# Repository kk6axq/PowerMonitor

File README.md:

# Power Monitor
This is a power management board for small robotics applications. This project was
developed as part of an honors contract for EGR216, electrical fundamentals,
during my Spring 2021 semester at Arizona State University, under the guidance
of Dr. Ayan Mallik.

# Purpose
The purpose of this project was to interface with a LiPo battery for a robotics
project I am developing in another course. The purpose of the board was to
prevent issues stemming from over discharge of the battery or accidental shorting.
As LiPo batteries are capable of delivering a large amount of current,
I wanted to prevent circuit damage in the case of short circuit conditions while
also preventing battery damage if I forgot to turn off the robot.
Additionally, I wanted to explore an alternative to the LM7805 I had used in
previous projects to provide a high current 5V supply for a planned payload bay
on the robot.
# Features
* Variety of current protection features:
  * Overcurrent up to 10A
  * Overvoltage detection up to 25V
  * Undervoltage detection
  * Short circuit protection
* Independent load control. Load, and 5V load supply can be switched on or off by the onboard microcontroller.
* Provides 5V at up to 3A and 12V at up to 10A burst.
* Dual power supplies for load and onboard microcontroller.
* Serial based monitoring and control of load switch, power status, and fault conditions.
* Onboard RGB LED for status indication
* Open source software.
* Hardware schematic and layout is open source. Project files are currently not available due to licensing restrictions.
# Design Criteria
* 12V power source or 3s LiPo battery
* Provide 12V at 4.2A from battery and 5V at 1.5A
* Monitor for fault conditions, including overvoltage, undervoltage, overcurrent, and short circuit
* Report faults to the robot's main microcontroller

# Core components:
* ATTiny88 microcontroller programmed with Arduino and the ATTinyCore
* ACS722 Current Sensor with +/- 10A current measuring capacity
* Voltage divider based voltage sensor with 25V measuring capability
* Dual LM2576 5V buck converter
* MIC5504 3.3V regulator for current sensor
* Si4435 P-Channel MOSFET for short circuit protection and load switching

# Repository Structure:
The repository is organized by folder, as shown below.
## Hardware
The hardware folder contains the KiCAD project files and output Gerbers and PDFs
for easy viewing. It includes:
* PDF schematic
* STEP file of PCB
* Bill of Materials
* Interactive HTML BOM for PCB assembly
* KiCAD project files
* Archive of Gerber board files and PDF of PCB layers

## Software
The software folder contains the code used to enable the power management behaviors.
## Docs
The docs folder contains documentation of the digital communications protocol and an explanation of the operation of the device.

# License
This project is copyright (C) 2021 by Lukas Severinghaus. It is licensed under the GNU GPLV3.

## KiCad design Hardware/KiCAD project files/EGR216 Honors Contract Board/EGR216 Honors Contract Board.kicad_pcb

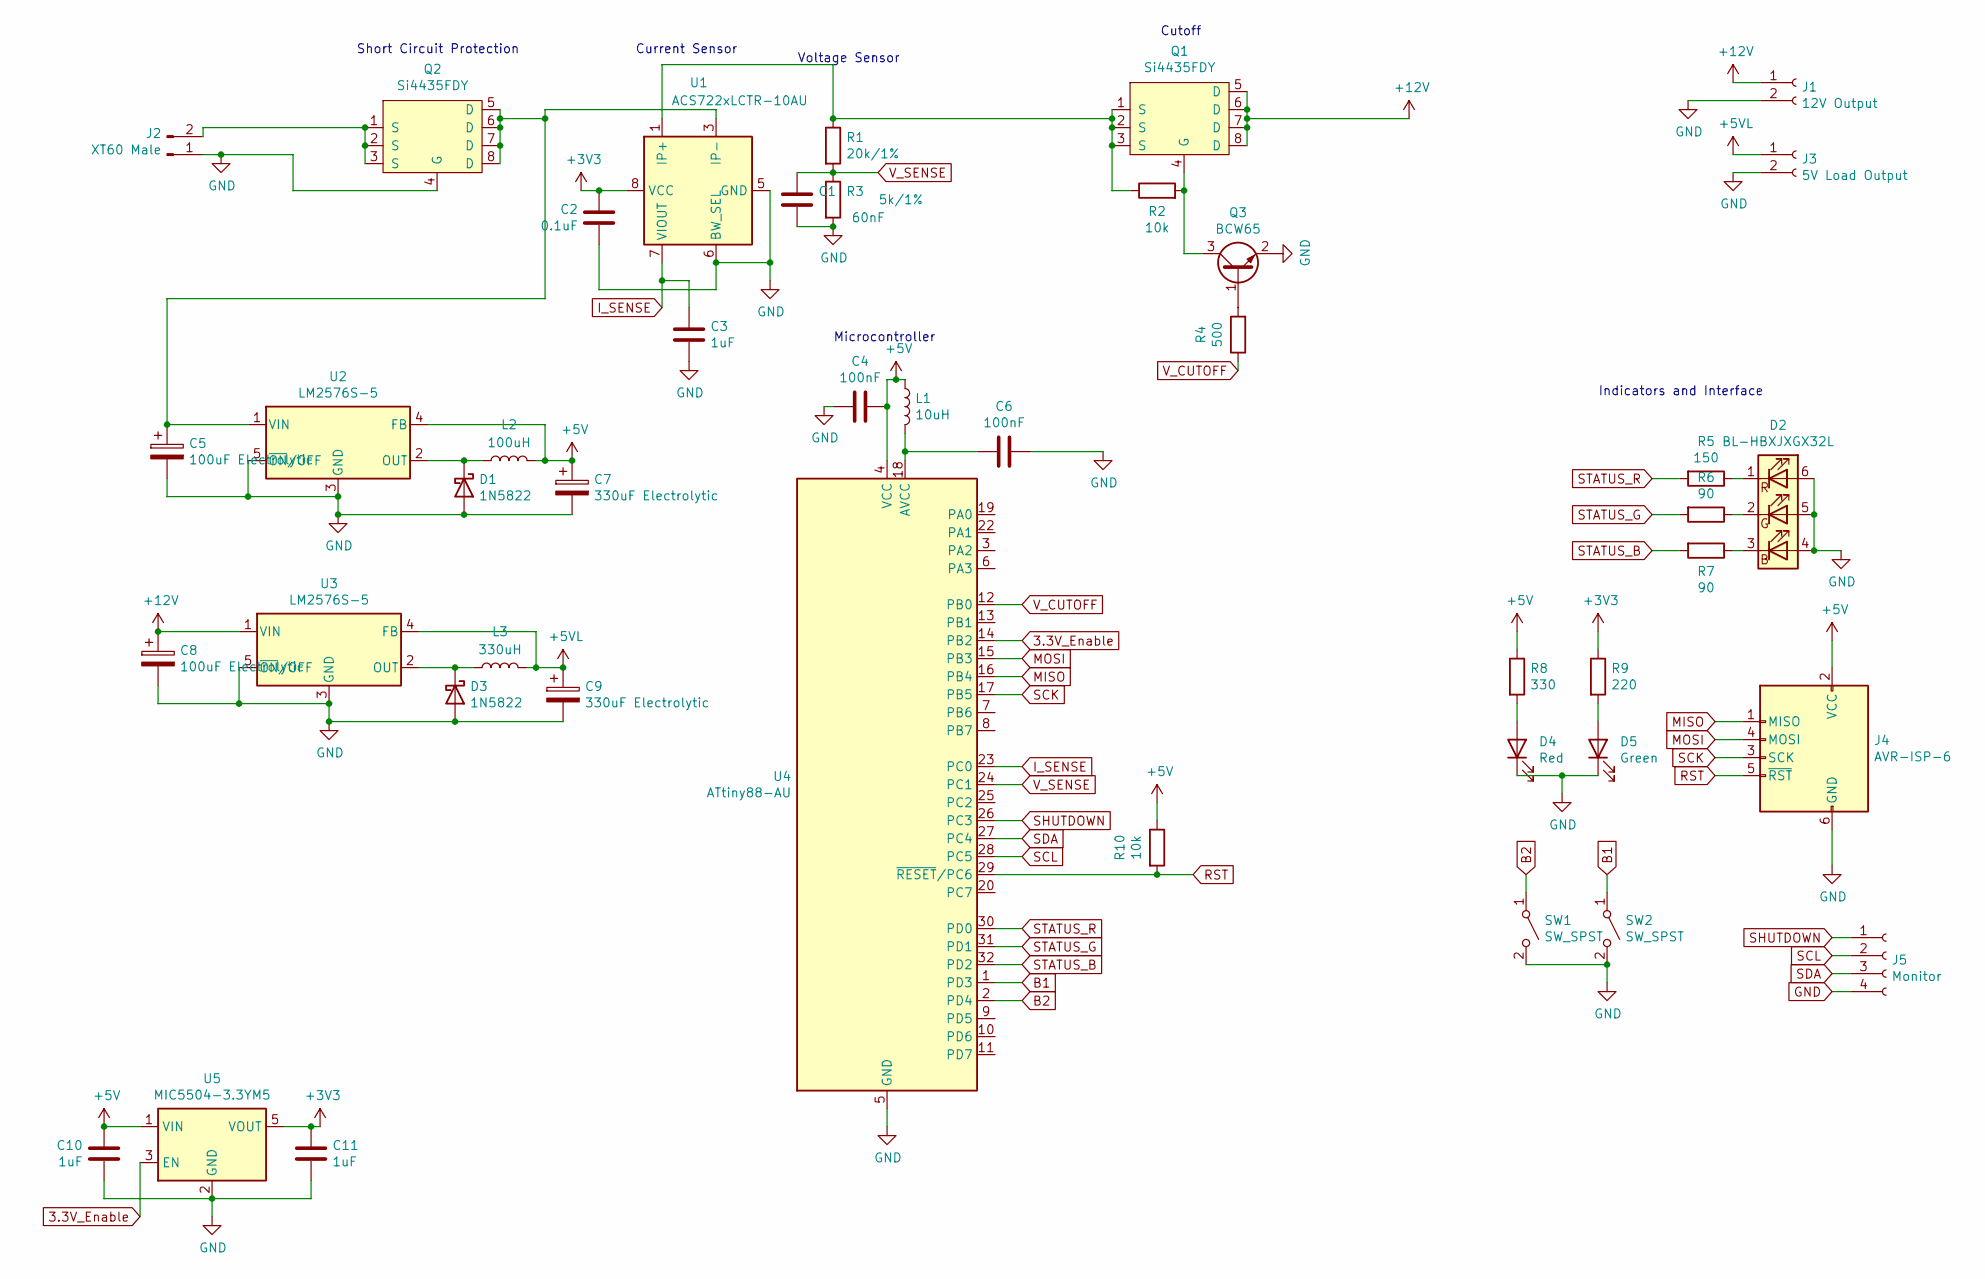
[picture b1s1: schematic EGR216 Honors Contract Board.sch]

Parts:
C1: 60nF; C_1206_3216Metric_Pad1.42x1.75mm_HandSolder
C2: 0.1uF; C_1206_3216Metric_Pad1.42x1.75mm_HandSolder
C3, C10, C11: 1uF; C_1206_3216Metric_Pad1.42x1.75mm_HandSolder
C4, C6: 100nF; C_1206_3216Metric_Pad1.42x1.75mm_HandSolder
C5, C8: 100uF Electrolytic; CP_Elec_8x10
C7, C9: 330uF Electrolytic; CP_Elec_8x5.4
D1, D3: 1N5822; D_DO-15_P15.24mm_Horizontal
D2: BL-HBXJXGX32L
D4: Red; LED_1206_3216Metric_Pad1.42x1.75mm_HandSolder
D5: Green; LED_1206_3216Metric_Pad1.42x1.75mm_HandSolder
J1: 12V Output; SolderWire-2.5sqmm_1x02_P7.2mm_D2.4mm_OD3.6mm_SMD
J2: XT60 Male; AMASS_XT60-M_1x02_P7.20mm_Vertical
J3: 5V Load Output; SolderWire-2.5sqmm_1x02_P7.2mm_D2.4mm_OD3.6mm_SMD
J4: AVR-ISP-6; PinHeader_2x03_P2.54mm_Vertical
J5: Monitor; PinHeader_1x04_P2.54mm_Vertical
L1: 10uH; L_1206_3216Metric_Pad1.42x1.75mm_HandSolder
L2: 100uH; L_1206_3216Metric_Pad1.42x1.75mm_HandSolder
L3: 330uH; Inductor-Murata-6000B
Q1, Q2: Si4435FDY; SOIC-8-1EP_3.9x4.9mm_P1.27mm_EP2.29x3mm
Q3: BCW65; SOT-23
R1: 20k/1%; R_1206_3216Metric_Pad1.42x1.75mm_HandSolder
R2, R10: 10k; R_1206_3216Metric_Pad1.42x1.75mm_HandSolder
R3: 5k/1%; R_1206_3216Metric_Pad1.42x1.75mm_HandSolder
R4: 500; R_1206_3216Metric_Pad1.42x1.75mm_HandSolder
R5: 150; R_1206_3216Metric_Pad1.42x1.75mm_HandSolder
R6, R7: 90; R_1206_3216Metric_Pad1.42x1.75mm_HandSolder
R8: 330; R_1206_3216Metric_Pad1.42x1.75mm_HandSolder
R9: 220; R_1206_3216Metric_Pad1.42x1.75mm_HandSolder
SW1, SW2: SW_SPST; PinHeader_1x02_P2.54mm_Vertical
U1: ACS722xLCTR-10AU; SOIC-8_3.9x4.9mm_P1.27mm
U2, U3: LM2576S-5; TO-263-5_TabPin3
U4: ATtiny88-AU; TQFP-32_7x7mm_P0.8mm
U5: MIC5504-3.3YM5; SOT-23-5

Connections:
3.3V_Enable: U4.14 (PB2), U5.3 (EN)
+3V3: C2.1, C11.1, R9.1, U1.8 (VCC), U5.5 (VOUT)
+5V: C4.2, C7.1, C10.1, J4.2 (VCC), L1.1, L2.2, R8.1, R10.1, U2.4 (FB), U4.4 (VCC), U5.1 (VIN)
+5VL: C9.1, J3.1, L3.2, U3.4 (FB)
+12V: C8.1, J1.1, Q1.5 (D), Q1.6 (D), Q1.7 (D), Q1.8 (D), U3.1 (VIN)
B1: SW2.1 (A), U4.1 (PD3)
B2: SW1.1 (A), U4.2 (PD4)
I_SENSE: C3.1, U1.7 (VIOUT), U4.23 (PC0)
MISO: J4.1 (MISO), U4.16 (PB4)
MOSI: J4.4 (MOSI), U4.15 (PB3)
unnamed: C5.1, Q2.5 (D), Q2.6 (D), Q2.7 (D), Q2.8 (D), U1.3 (IP-), U1.4 (IP-), U2.1 (VIN)
unnamed: C6.1, L1.2, U4.18 (AVCC)
unnamed: D1.1 (K), L2.1, U2.2 (OUT)
unnamed: D2.1 (RK), R5.1
unnamed: D2.2 (GK), R6.1
unnamed: D2.3 (BK), R7.1
unnamed: D3.1 (K), L3.1, U3.2 (OUT)
unnamed: D4.2 (A), R8.2
unnamed: D5.2 (A), R9.2
unnamed: J2.2, Q2.1 (S), Q2.2 (S), Q2.3 (S)
unnamed: Q1.1 (S), Q1.2 (S), Q1.3 (S), R1.1, R2.1, U1.1 (IP+), U1.2 (IP+)
unnamed: Q1.4 (G), Q3.3 (C), R2.2
unnamed: Q3.1 (B), R4.2
RST: J4.5 (~RST), R10.2, U4.29 (~RESET~/PC6)
SCK: J4.3 (SCK), U4.17 (PB5)
SCL: J5.2, U4.28 (PC5)
SDA: J5.3, U4.27 (PC4)
SHUTDOWN: J5.1, U4.26 (PC3)
STATUS_B: R7.2, U4.32 (PD2)
STATUS_G: R6.2, U4.31 (PD1)
STATUS_R: R5.2, U4.30 (PD0)
V_CUTOFF: R4.1, U4.12 (PB0)
V_SENSE: C1.1, R1.2, R3.1, U4.24 (PC1)

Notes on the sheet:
Short Circuit Protection
Current Sensor
Voltage Sensor
Microcontroller
Indicators and Interface
Cutoff

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
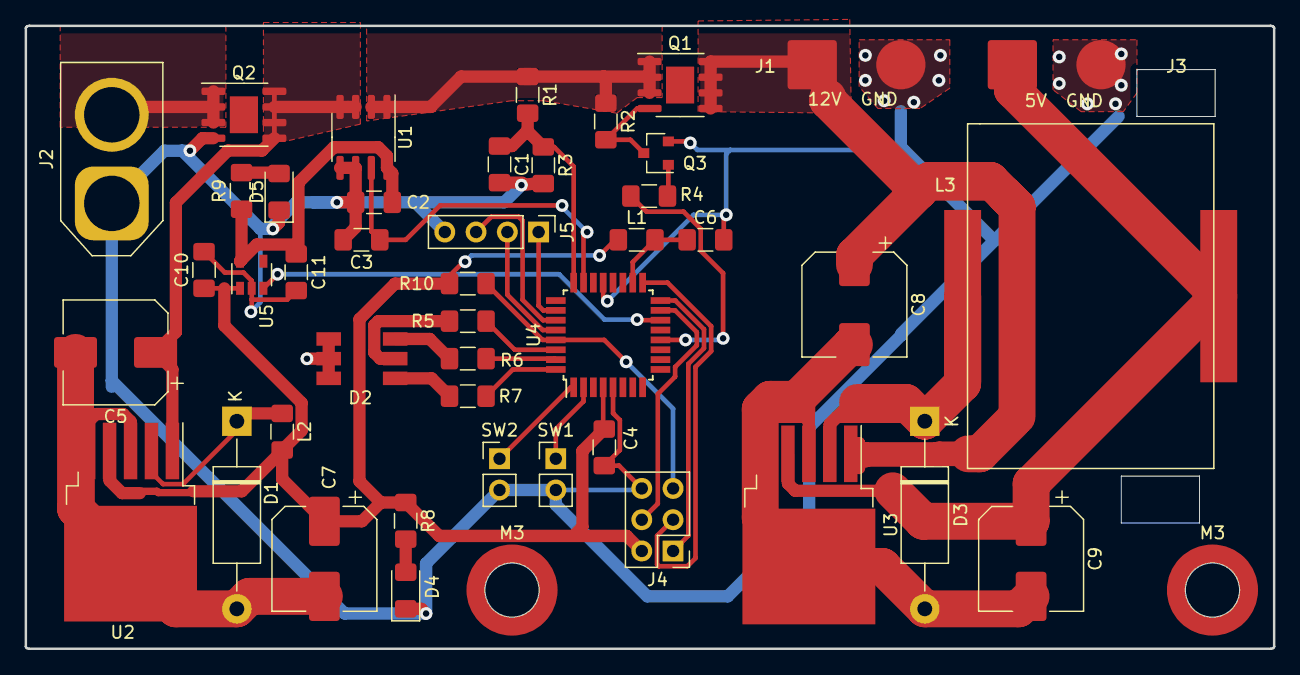
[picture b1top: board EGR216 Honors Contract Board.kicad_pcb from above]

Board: 2 copper layers, 101.4 x 50.6 mm, 46 parts (0 on the bottom side), 35 nets.

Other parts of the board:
M3, M3#2: Mounting_Wuerth_WA-SMSI-M3_H2mm_9774020360

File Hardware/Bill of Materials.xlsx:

Universal Reference | Board Reference | Qty | Actual Qty | Value | Footprint | Part number | Price | Note |  | One board price |  | Total purchase price
Power THT C1 | C1 | 1 | 10 | 60nF | THT | 399-14063-ND | 0.25900000000000001 |  |  | 0.25900000000000001 |  | 2.59
Power THT C11 C10 C3 | C11 C10 C3 | 3 | 15 | 1uF | THT | 445-8395-ND | 0.22 |  |  | 0.66 |  | 3.3
Power THT C2 | C2 | 1 | 10 | 0.1uF | THT | 399-4151-ND | 0.157 |  |  | 0.157 |  | 1.57
Power THT C5 C8 | C5 C8 | 2 | 10 | 100uF Electrolytic | THT | 1572-1659-ND | 0.126 |  |  | 0.252 |  | 1.26
Power THT C6 C4 | C6 C4 | 2 | 10 | 100nF | THT | 399-4151-ND | 0.157 |  |  | 0.314 |  | 1.57
Power THT C7 C9 | C7 C9 | 2 | 10 | 330uF Electrolytic | THT | 1572-1437-ND | 0.215 |  |  | 0.43 |  | 2.15
Power THT D1 D3 | D1 D3 | 2 |  | 1N5822 | THT | 497-11370-1-ND | 0.28199999999999997 |  |  | 0.56399999999999995 |  | 0
Power THT D2 | D2 | 1 | 1 | BL-HBXJXGX32L | 5050 | BL-HBXJXGX32LCT-ND | 0.40100000000000002 | Use SMD |  | 0.40100000000000002 |  | 0.40100000000000002
Power THT D4 | D4 | 1 | 10 |  |  |  |  | Already Have |  | 0 |  | 0
Power THT D5 | D5 | 1 | 10 |  |  |  |  | Already Have |  | 0 |  | 0
Power THT J1 | J1 | 1 |  | 12V Output |  |  |  | Already Have |  | 0 |  | 0
Power THT J2 | J2 | 1 |  | XT60 Male | Amass:AMASS_XT60-M_1x02_P7.20mm_Vertical |  |  | Already Have |  | 0 |  | 0
Power THT J3 | J3 | 1 |  | 5V Load Output | Connector_PinHeader_2.54mm:PinHeader_1x02_P2.54mm_Vertical |  |  | Already Have |  | 0 |  | 0
Power THT J4 | J4 | 1 | 5 | AVR-ISP-6 | 2x3 2.54 |  |  | Already Have |  | 0 |  | 0
Power THT J5 | J5 | 1 |  | Monitor | 2.54 |  |  | Already Have |  | 0 |  | 0
Power THT L1 | L1 | 1 | 5 | 10uH | THT | 78F100J-TR-RCTR-ND | 0.252 |  |  | 0.252 |  | 1.26
Power THT L2 L3 | L2 L3 | 2 | 3 | 330uH | THT | 595-1734-ND | 2.54 |  |  | 5.08 |  | 7.62
Power THT Q2 Q1 | Q2 Q1 | 2 | 10 | Si4435FDY | SOIC8 | SI4435FDY-T1-GE3CT-ND | 0.38200000000000001 | Use SMD |  | 0.76400000000000001 |  | 3.8200000000000003
Power THT Q3 | Q3 | 1 | 10 | BC856 | SOT23-3 | BC856BLT3GOSCT-ND | 8.7999999999999995E-2 | Use SMD |  | 8.7999999999999995E-2 |  | 0.87999999999999989
Power THT R1 | R1 | 1 | 5 | 20k/1% | THT | RNF14FTD20K0TR-ND | 0.1 |  |  | 0.1 |  | 0.5
Power THT R10 R2 | R10 R2 | 2 | 20 | 10k |  |  |  | Already have |  | 0 |  | 0
Power THT R3 | R3 | 1 | 5 | 5k/1% | THT | 1135-1619-ND | 0.5 |  |  | 0.5 |  | 2.5
Power THT R4 | R4 | 1 | 10 | 500 | THT | CF14JT470RCT-ND | 3.5999999999999997E-2 | 470ohms |  | 3.5999999999999997E-2 |  | 0.36
Power THT R5 | R5 | 1 | 10 | 150 | THT | CF14JT150RCT-ND | 3.5999999999999997E-2 |  |  | 3.5999999999999997E-2 |  | 0.36
Power THT R6 R7 | R6 R7 | 2 | 10 | 90 | THT | CF14JT100RCT-ND | 3.5999999999999997E-2 | 100ohms |  | 7.1999999999999995E-2 |  | 0.36
Power THT R8 | R8 | 1 | 10 | 330 |  |  |  | Already Have |  | 0 |  | 0
Power THT R9 | R9 | 1 | 10 | 220 |  |  |  | Already Have |  | 0 |  | 0
Power THT SW2 SW1 | SW2 SW1 | 2 | 2 | SW_SPST |  |  |  | Already Have |  | 0 |  | 0
Power THT U1 | U1 | 1 | 1 | ACS722xLCTR-10AU | SOIC8 | 620-1636-1-ND | 3.94 | Use SMD |  | 3.94 |  | 3.94
Power THT U2 U3 | U2 U3 | 2 | 3 | LM2576S-5 | THT | 576-1518-5-ND | 2.0099999999999998 |  |  | 4.0199999999999996 |  | 6.0299999999999994
Power THT U4 | U4 | 1 | 5 | ATtiny88-AU | THT | ATTINY88-PU-ND | 1.8 |  |  | 1.8 |  | 9
Power THT U5 | U5 | 1 | 10 | MIC5504-3.3YM5 | SOT-23-5 | 576-4764-1-ND | 0.13 | Use SMD |  | 0.13 |  | 1.3
 |  |  |  |  |  |  |  |  | Total | 19.854999999999997 | Total | 50.770999999999994

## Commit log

2021-03-29 Second initial commit
2021-03-29 Update code to enable machine readability
    Also removed some unnecessary debug printouts.
2021-03-29 Add and reorganize the hardware files.
    Received permission to upload the KiCAD footprints with the project, so added the project source files.
2021-03-29 Update documentation
    Added better documentation for protocol, background, and future work.
2021-04-07 Add benchmark graphs
2021-04-07 Add benchmarking data
2021-09-24 Add photos
2021-09-24 Add schematic image
2021-09-24 Add photos to README
2021-09-24 Fix whitespace
2021-09-24 Add block diagram photo
